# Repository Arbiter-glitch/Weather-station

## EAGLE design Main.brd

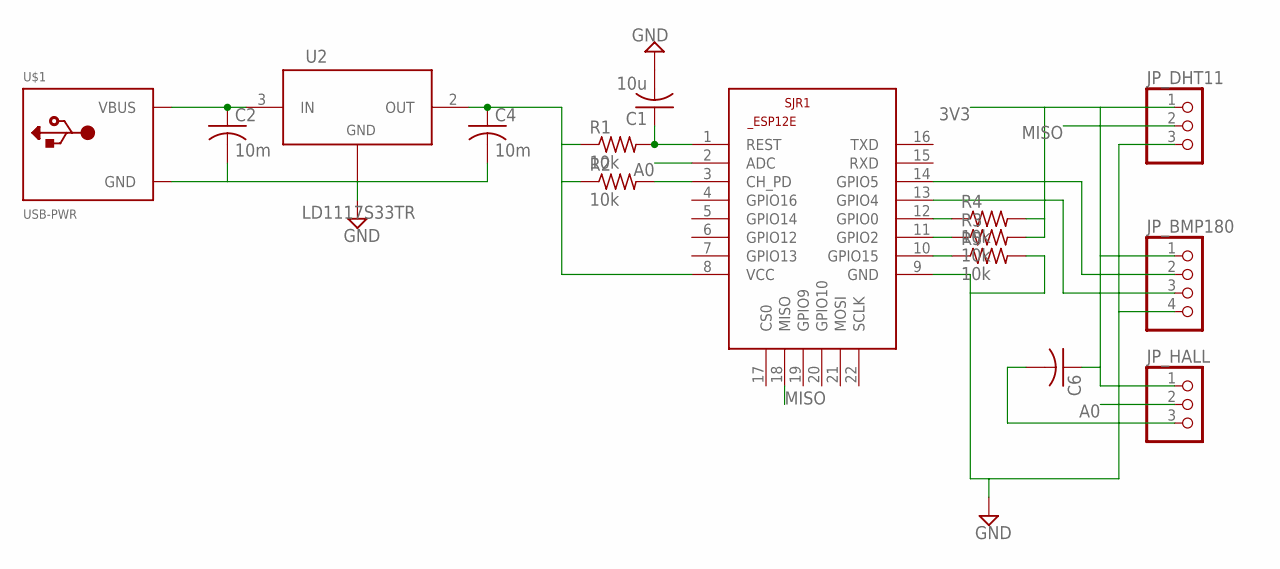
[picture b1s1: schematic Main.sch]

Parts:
C1: 10u; C0805
C2, C4: 10m; C0805
C6: C-USC0805; C0805
JP_BMP180: PINHD-1X4/90; 1X04/90
JP_DHT11: PINHD-1X3/90; 1X03/90
JP_HALL: PINHD-1X3/90; 1X03/90
R1, R2, R3, R4, R5: 10k; M1406
SJR1: ESP8266-12EESP12E; ESP8266-ESP12E
U2: LD1117S33TR; SOT-223
U$1: USB-PWR; USB-MINIB-THM-MOLEX-PWRONLY

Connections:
3V3: C4.1, C6.1, JP_BMP180.1, JP_DHT11.1, JP_HALL.1, R1.1, R2.1, R3.2, R4.2, SJR1.8 (VCC), U2.2 (OUT), U2.4
A0: JP_HALL.2, SJR1.2 (ADC)
GND: C1.2, C2.2, C4.2, C6.2, JP_BMP180.4, JP_DHT11.3, JP_HALL.3, R5.2, SJR1.9 (GND), U2.1 (ADJ/GND), U$1.GND
MISO: JP_DHT11.2, SJR1.18 (MISO)
unnamed: C2.1, U2.3 (IN), U$1.VBUS
unnamed: R2.2, SJR1.3 (CH_PD)
unnamed: C1.1, R1.2, SJR1.1 (REST)
unnamed: R4.1, SJR1.12 (GPIO0)
unnamed: R3.1, SJR1.11 (GPIO2)
unnamed: R5.1, SJR1.10 (GPIO15)
unnamed: JP_BMP180.3, SJR1.13 (GPIO4)
unnamed: JP_BMP180.2, SJR1.14 (GPIO5)

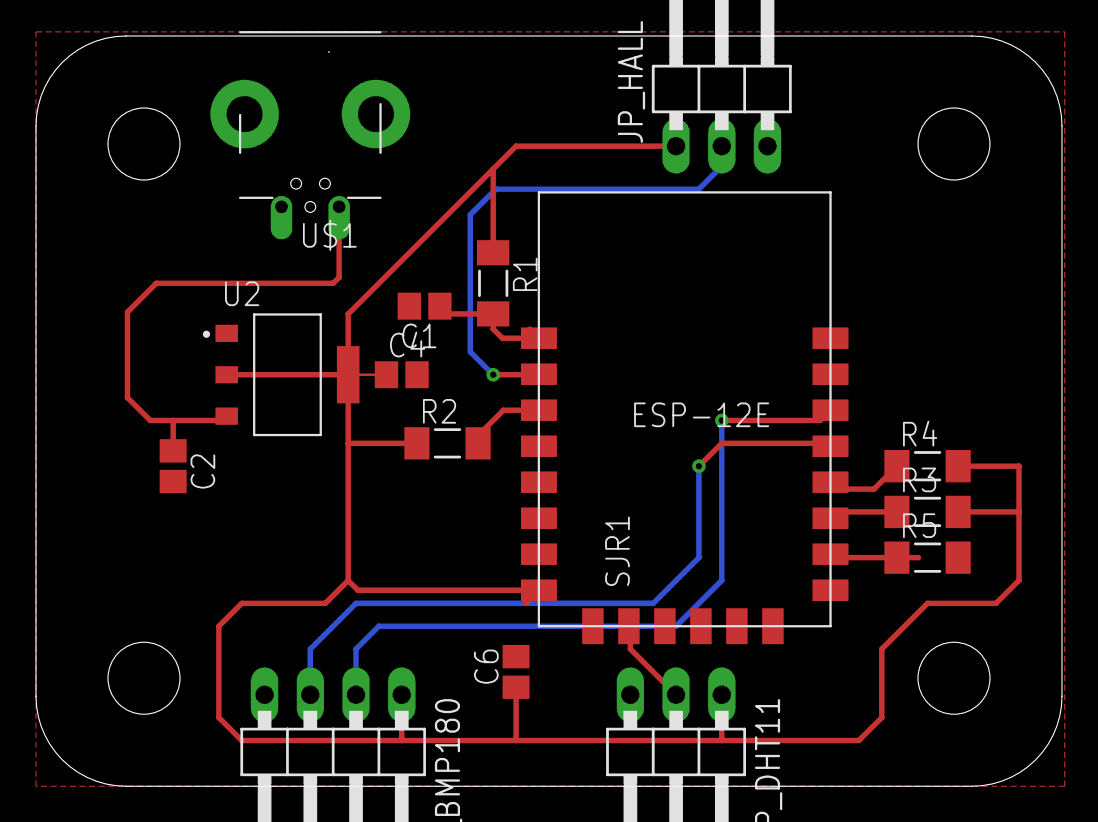
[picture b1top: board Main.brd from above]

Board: 2 copper layers, 57.0 x 41.7 mm, 15 parts (0 on the bottom side), 12 nets.
